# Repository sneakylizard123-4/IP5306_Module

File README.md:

# IP5306 Power-Bank Module

A small USB power bank module that uses a 1S lithium battery and outputs a regulated 5V supply.

This board is a small power bank module built around the Injoinic IP5306 SoC. It takes USB-C input to charge a lithium battery and outputs a regulated 5V rail from a USB-A port in output mode. It is a standalone module with no MCU, only a power button and 4-LED charge/fuel gauge handle all user input. I built it to have a fully integrated power path solution that avoids the complexity of discrete charger and boost circuits.

## Features

- IP5306: fully integrated 2.1A charger and 2.4A discharger with built-in boost converter.
- USB-C input for charging, USB-A output for 5V output.
- 1S Li-ion/LiPo battery connection via JST PH 2-pin header.
- Power button for power on/off and battery gauge.
- 4-LED charge/fuel gauge.
- 1uH shielded inductor for the boost converter.

## How It Works

The IP5306 has an entire power path inside of it. On the input side, 5v from USB-C charges a connected 1S lithium battery through the IP5306's built-in 2.1A charger. On the output side, the chip boosts the battery voltage to a regulated 5V output rail when in power-bank mode. The boost inductor and output capacitors form the boost converter, while the battery, LED, and decoupling capacitors support the charge path, gauge, and IC supply. Pressing the KEY button powers the module on/off and goes through the fuel gauge.

| Block | Part | Role |
|-------|------|------|
| Power | IP5306 | Power Bank SoC with battery charger, boost regulator, 5V rail, charge gauge |
| Input | HRO TYPE-C-31-M-12 | USB-C receptacle for charging input |
| Output | Connfly DS1095 | USB-A receptacle for 5V power-bank output |
| Battery | B2B-PH-K | JST PH 2-pin connector to 1S Li-ion/LiPo battery |
| Inductor | Coilcraft XFL4020-102MEC | 1uH boost converter inductor |
| Capacitors | 10uF x4, 22uF x3  Boost output + IC decoupling |
| Resistors | 5.1k x2, 10k x3, 2 ohm x2 | USB-C CC pulldowns, biasing, LED current limit |
| LEDs | 0805 x6 | Charge and boost status indicators |
| Button | Panasonic EVQPUM | Power on/off + fuel gauge on KEY pin |

### Power Tree

The power path flows from the USB-C input through the IP5306 charger into the battery, and from the battery through the IP5306 boost converter out to the USB-A port. The KEY button and LED gauge hang off the chip's control pins.

| Direction | Path |
|-----------|------|
| Charge | USB-C (5V) -> IP5306 charger -> 1S battery |
| Discharge | 1S battery -> IP5306 boost -> 5V USB-A out |

## Board

*Top layer with the tracks, pads and ground pour.*

*Bottom layer with the stitched ground return path.*

## Usage

1. Connect a 3.7V Li-ion/LiPo battery to the JST PH connector. 
2. Connect the USB-C to charge the battery. the LEDs indicate charge state. 
3. Connect a device to the USB-A port and press the power button to enable the 5V output; short presses cycle the LED fuel gauge and a long press toggles the module on/off.

| Pin | Function |
|-----|----------|
| BAT+ / BAT- | JST PH battery connections (1S Li-ion/LiPo) |
| KEY | Power button input |
| GND | Common ground |

## Repository Structure

```
├── kicad/            # PCB source files
│   └── production/   # Gerbers + drill files
├── cad/              # .step export + native CAD source
├── firmware/         # Firmware source code
├── images/           # Renders, PCB screenshots, build photos
├── BOM.csv           # Bill of materials w/ links + total cost line
└── JOURNAL.md        # Work journal
```

## Cost

| Item | Cost |
|------|------|
| PCB | $3.20 |
| Shipping | $1.50 |
| **PCB subtotal** | **$4.70** |
| Components | $12.99 |
| **Total** | **$17.69** |

*Full BOM available in BOM.csv*

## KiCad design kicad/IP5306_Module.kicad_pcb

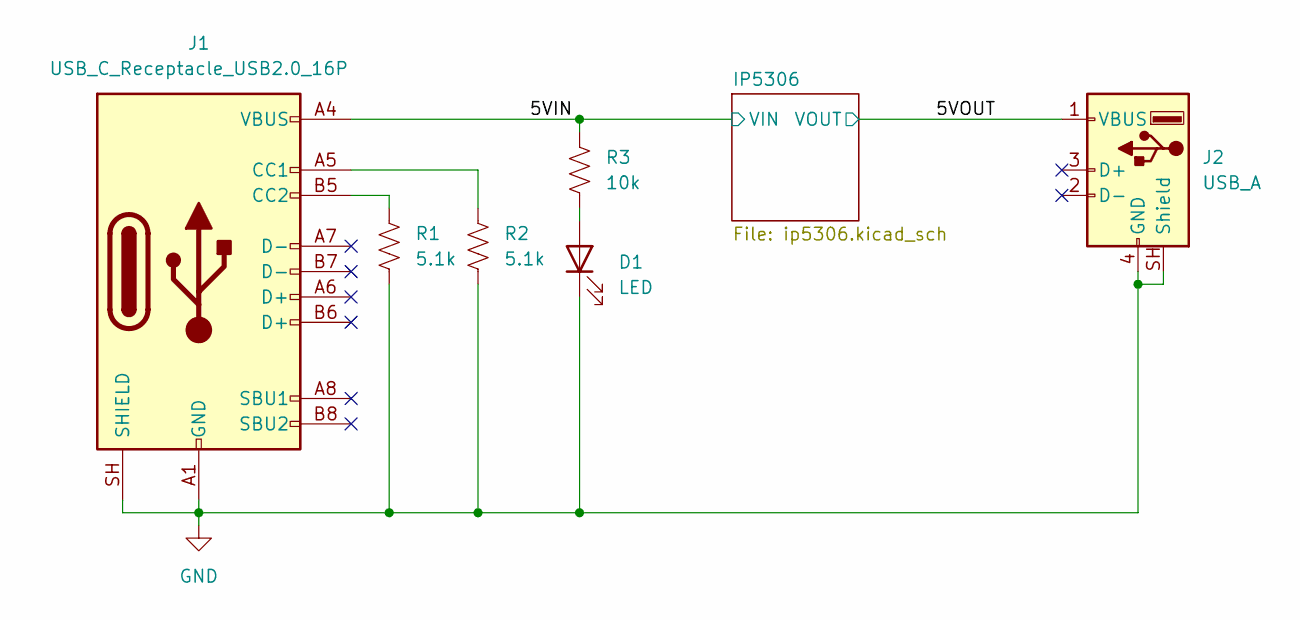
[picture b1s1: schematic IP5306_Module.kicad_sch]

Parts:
D1: LED; LED_0805_2012Metric
J1: USB_C_Receptacle_USB2.0_16P; USB_C_Receptacle_HRO_TYPE-C-31-M-12
J2: USB_A; USB_A_Connfly_DS1095
R1, R2: 5.1k; R_0805_2012Metric
R3: 10k; R_0805_2012Metric

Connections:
/5VIN: J1.A4 (VBUS), J1.A9 (VBUS), J1.B4 (VBUS), J1.B9 (VBUS), R3.1; also elsewhere on the board
/5VOUT: J2.1 (VBUS); also elsewhere on the board
GND: D1.1 (K), J1.A1 (GND), J1.A12 (GND), J1.B1 (GND), J1.B12 (GND), J1.SH (SHIELD), J2.4 (GND), J2.SH (Shield), R1.2, R2.2; also elsewhere on the board
unnamed: D1.2 (A), R3.2
unnamed: J1.A5 (CC1), R2.1
unnamed: J1.B5 (CC2), R1.1

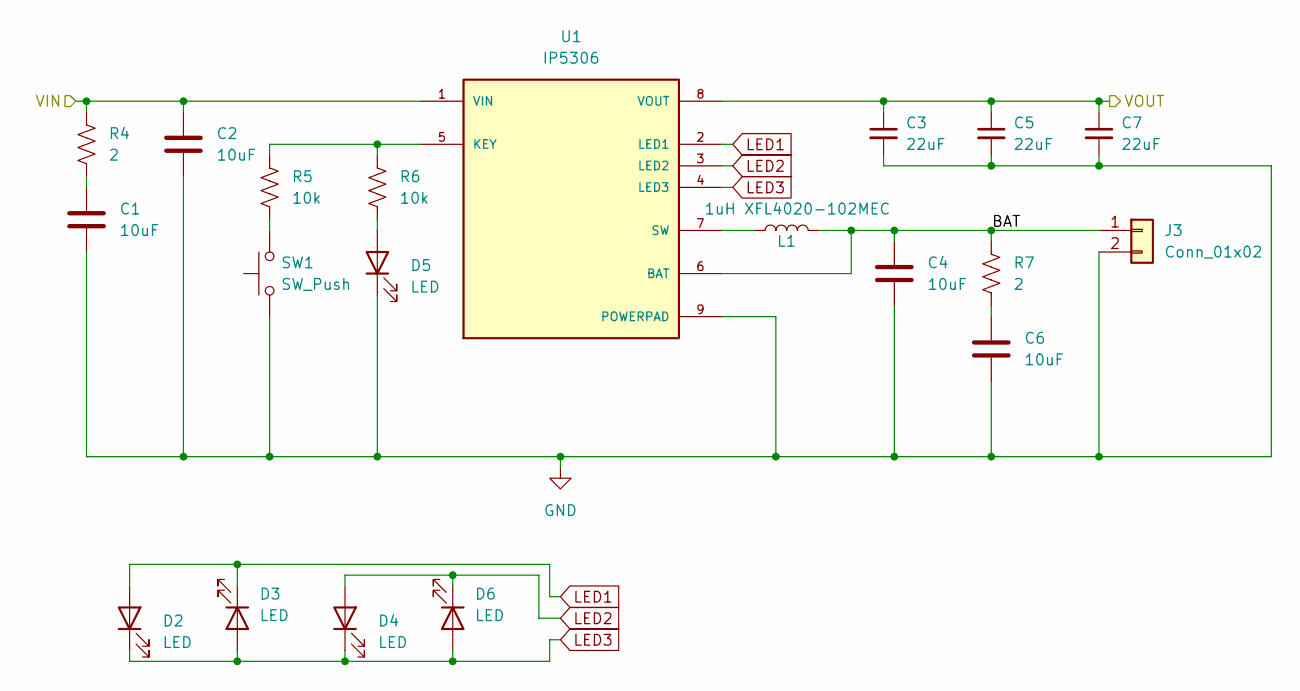
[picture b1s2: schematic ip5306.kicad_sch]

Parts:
C1, C2, C4, C6: 10uF; C_0805_2012Metric
C3, C5, C7: 22uF; C_0805_2012Metric
D2, D3, D4, D5, D6: LED; LED_0805_2012Metric
J3: Conn_01x02; JST_PH_B2B-PH-K_1x02_P2.00mm_Vertical
L1: 1uH XFL4020-102MEC; L_Coilcraft_XxL4020
R4, R7: 2; R_0805_2012Metric
R5, R6: 10k; R_0805_2012Metric
SW1: SW_Push; Panasonic_EVQPUM_EVQPUD
U1: IP5306; SOP127P600X165-9N; PARTREV 1.31

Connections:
/5VIN: C2.1, R4.1, U1.1 (VIN); also elsewhere on the board
/5VOUT: C3.1, C5.1, C7.1, U1.8 (VOUT); also elsewhere on the board
/IP5306/BAT: C4.1, J3.1, L1.2, R7.1, U1.6 (BAT)
GND: C1.2, C2.2, C3.2, C4.2, C5.2, C6.2, C7.2, D5.1 (K), J3.2, SW1.1, U1.9 (POWERPAD); also elsewhere on the board
LED1: D2.2 (A), D3.1 (K), U1.2 (LED1)
LED2: D4.2 (A), D6.1 (K), U1.3 (LED2)
LED3: D2.1 (K), D3.2 (A), D4.1 (K), D6.2 (A), U1.4 (LED3)
unnamed: C1.1, R4.2
unnamed: C6.1, R7.2
unnamed: D5.2 (A), R6.2
unnamed: R5.2, SW1.2
unnamed: R5.1, R6.1, U1.5 (KEY)
unnamed: L1.1, U1.7 (SW)

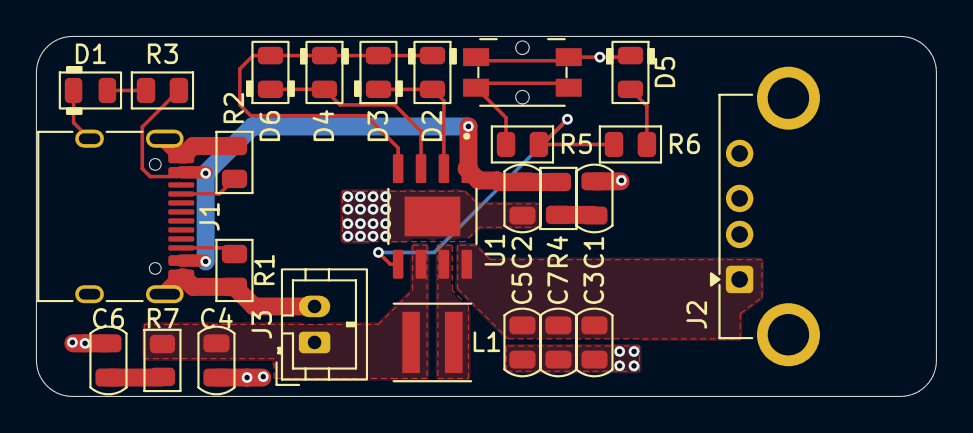
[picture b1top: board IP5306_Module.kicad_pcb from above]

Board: 2 copper layers, 50.0 x 20.0 mm, 26 parts (0 on the bottom side), 16 nets.

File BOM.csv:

Ref,Value,LCSC#,MPN,Manufacturer,Footprint,Qty,Unit Price($),Ext Price($),Supplier Link
C1,C2,C4,C6,10uF 25V X5R,C15850,CL21A106KAYNNNE,Samsung Electro-Mechanics,0805,20,0.0871,1.74,https://www.lcsc.com/product-detail/C15850.html
C3,C5,C7,22uF 25V X5R,C86816,GRM21BR61E226ME44L,muRata,0805,10,0.0698,0.70,https://www.lcsc.com/product-detail/C86816.html
D1,D2,D3,D4,D5,D6,Orange LED 0805,C965813,XL-2012UOC,XINGLIGHT,0805,50,0.0096,0.48,https://www.lcsc.com/product-detail/C965813.html
J1,USB-C Receptacle 16P,C165948,TYPE-C-31-M-12,Korean Hroparts Elec,SMD,5,0.1724,0.86,https://www.lcsc.com/product-detail/C165948.html
J2,USB-A Right Angle,C19944603,DS1095-WNR0,CONNFLY Elec,Through Hole,5,0.2076,1.04,https://www.lcsc.com/product-detail/C19944603.html
J3,JST PH 2P 2mm,C131337,B2B-PH-K-S(LF)(SN),JST,Through Hole,20,0.0356,0.71,https://www.lcsc.com/product-detail/C131337.html
L1,1uH Shielded Inductor,C5355380,XFL4020-102MEC,Coilcraft,SMD 4x4mm,1,2.5134,2.51,https://www.lcsc.com/product-detail/C5355380.html
R1,R2,5.1k 1% 0805,C27834,0805W8F5101T5E,UNI-ROYAL,0805,100,0.0065,0.65,https://www.lcsc.com/product-detail/C27834.html
R3,R5,R6,10k 1% 0805,C2907219,FRC0805F1002TS,FOJAN,0805,100,0.0035,0.35,https://www.lcsc.com/product-detail/C2907219.html
R4,R7,2R 1% 0805,C114246,RC0805FR-072RL,YAGEO,0805,50,0.0261,1.31,https://www.lcsc.com/product-detail/C114246.html
SW1,Tactile Switch 4.7x4.5mm,C388885,EVQPUD02K,PANASONIC,SMD,5,0.2299,1.15,https://www.lcsc.com/product-detail/C388885.html
U1,IP5306 ESOP-8,C181692,IP5306,INJOINIC,ESOP-8,5,0.2989,1.49,https://www.lcsc.com/product-detail/C181692.html
PCB,Bare PCB 5 pcs (JLCPCB special offer),,,JLCPCB,,5,0.64,3.20,
Shipping,,Global Standard (JLCPCB),,,,1,1.50,1.50,
Total,,,Components (LCSC) + PCB + shipping,,,,17.69,
